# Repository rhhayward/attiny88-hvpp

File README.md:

### Important

The code has been tested on a breadboard, and the original pcb has been
validated to work.  There were two changes made since ordering: 1. The
attiny88 footprint was not wide enough, so it was widened in REV002.
2. The 12v source had left and right reversed - that is fixed in REV003.

Caveat emptor:  If you order PCBs from this, be prepared for them not
to work.  You have been warned.

### ATTINY88 High Voltage Parallel Programmer

This project came from a bricked attiny88. I was changing the fuses, and after
one particular update, none of the methods to program or update fuses worked.
The programmer was unable even to read the signature or fuses. However, the code
was still working, albeit terribly slowly. An LED which previously blinked once
per second was taking minutes to complete a blink cycle. While ATTINY88
microcontrollers are inexpensive and could easily be replaced, I took it as a
challenge to unbrick this one. Reading the datasheet and online, a high voltage
parallel programmer was what was needed, but I couldn't find code or a
schematic, so I worked to get a hvpp programmer working.

This was validated working with a purple pi (off-brand rp2040), a 12v boost
regulator, and the aforementioned bricked ATTINY88. I was then able to use the
`WRITEFUS` command to unbrick the device.  I implemented a few additional
commands as well.  The entire suite of possible commands is not yet available,
but should be doable leveraging the primitives that are already implemented.

### How to

The wiring is laid out in the .ino file. The only additional circuitry is that
the 5v providing the ATTINY88's VCC and the 12v necessary for the RST pin are
switched using a transistor+mosfet. All other wiring is direct from the purple
pi to the ATTINY88.  You can see the full schematic in
`/kicad/attiny88-hvpp.kicad_sch`
(https://kicanvas.org/?github=https%3A%2F%2Fgithub.com%2Frhhayward%2Fattiny88-hvpp%2Ftree%2Fmain%2Fkicad).

Once wired, you canbuild and push the code to the purple pi. I have tested this
using the Arduino IDE 2 with the Raspberry Pi Pico profile which worked for me
with no trouble. With the code running, connect to the purple pi's USB Serial
port.  The code will always prefix its output with a `*`.  It will emit some
help on start.  Once it announces done, you can start issuing commands.

## Commands

* `READSIG` - read and display signature bytes
* `READCAL` - read and display calibration byte
* `READFUS` - read and display fuse and lock bytes
* `READFLA 0x<START> 0x<END>` - read and display flash from start to end
* `WRITEFUS 0x<low> 0x<high> 0x<extended>` - write low high and extended
  fuses, then read and display fuse and lock bytes

## Example execution

```
* starting up
* setting up pin modes and values
* setting up pin modes and values - DONE
* entering programming mode
* entering programming mode - DONE
* Commands:
* READSIG - read signature and write to stdout
* READCAL - read calibration byte and write to stdout
* READFUS - read fuses and lock bytes
* READFLA 0x<START> 0x<END> - read flash from START to END.  Each must be 4 hex digits.
* WRITEFUS 0x<LOW> 0x<HIGH> 0x<EXTENDED> - write LOW HIGH and EXTENDED fuses.  Each must be 2 hex digits.
* * * ready
```
```
READSIG
```
```
* SIGNATURE: 0x1E,0x93,0x11 IDENT: ATTINY88
```
```
READFUS
```
```
* FUSE l=0x37 h=0xDF x=0xFF LOCK 0xFF
```
```
READCAL
```
```
* calibration byte: 0x9D
```
```
READFLA 0x0000 0x0010
```
```
* start=0x0000 end=0x0010
* 0x0000   13c0 22c0 21c0 20c0 1fc0 1ec0 1dc0 1cc0  1bc0 1ac0 19c0 18c0 17c0 16c0 74c0 14c0
```

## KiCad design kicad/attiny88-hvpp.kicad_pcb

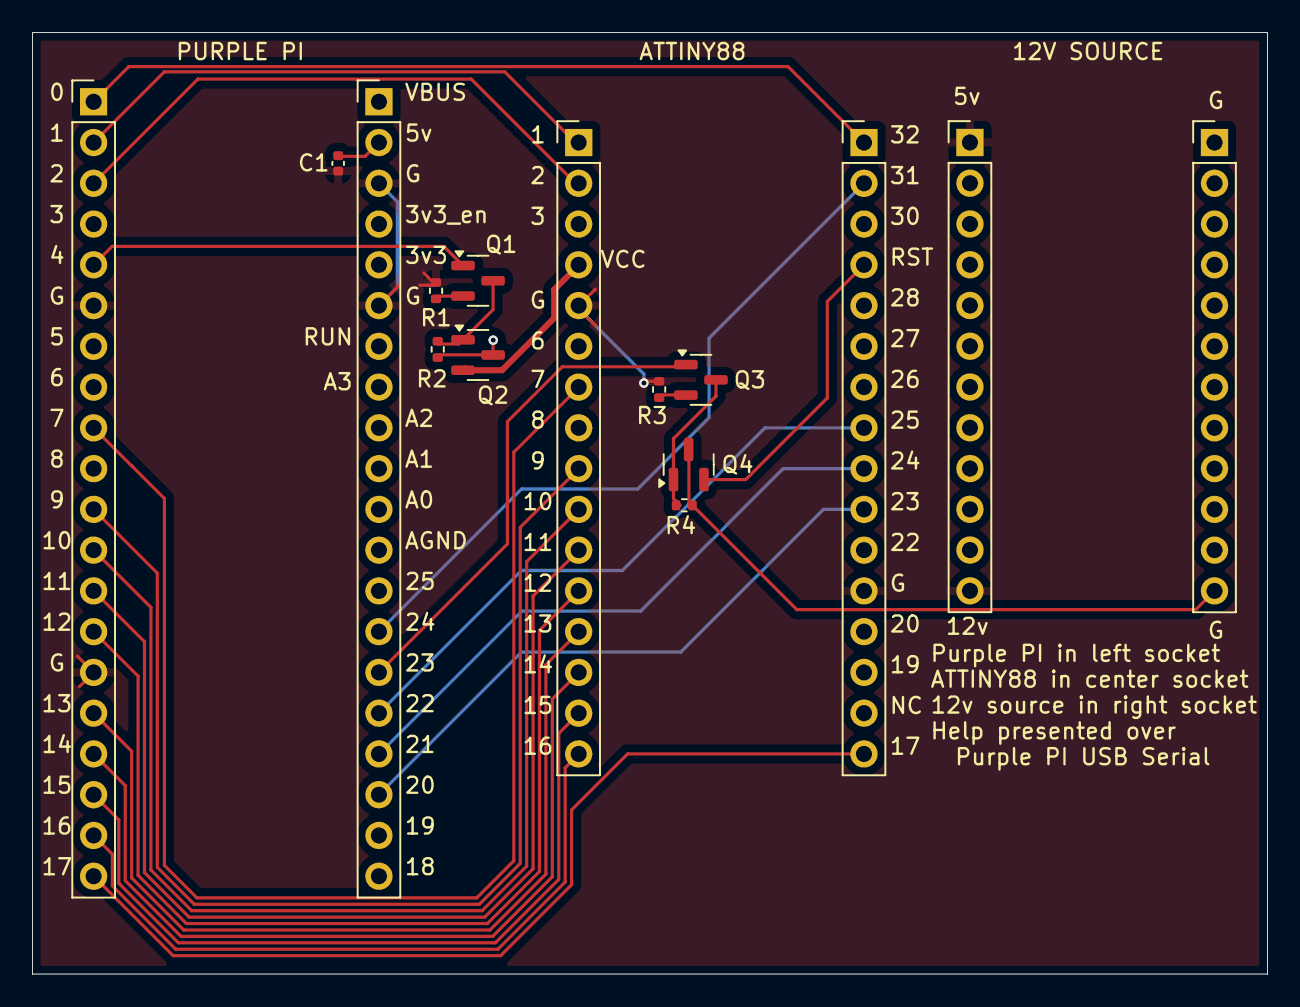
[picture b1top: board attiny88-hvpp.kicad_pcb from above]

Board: 2 copper layers, 77.0 x 58.7 mm, 15 parts (0 on the bottom side), 28 nets.

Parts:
C1: 1u; C_0402_1005Metric
J1: 12v_reg_left_neg; PinHeader_1x12_P2.54mm_Vertical
J2: 12v_reg_right_pos; PinHeader_1x12_P2.54mm_Vertical
J3: purle_pi_left; PinHeader_1x20_P2.54mm_Vertical
J4: purle_pi_right; PinHeader_1x20_P2.54mm_Vertical
J5: ATTINY88_LEFT; PinHeader_1x16_P2.54mm_Vertical
J6: ATTINY88_RIGHT; PinHeader_1x16_P2.54mm_Vertical
Q1, Q3: MMBT3904; SOT-23
Q2, Q4: IRLML6402; SOT-23
R1, R3: 2k2; R_0402_1005Metric
R2, R4: 220k; R_0402_1005Metric

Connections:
/5v: C1.1, J2.1, J4.2, Q2.3 (D), R2.2
/12v: J2.12, Q4.3 (D), R4.2
/ATT5v: J5.4, Q2.2 (S)
/BS1: J3.3, J5.2
/BS2: J4.16, J6.8
/CLKI: J3.9, J5.7
/DATA0: J4.17, J6.9
/DATA1: J4.18, J6.10
/DATA2: J3.20, J6.16
/DATA3: J3.19, J5.16
/DATA4: J3.18, J5.15
/DATA5: J3.17, J5.14
/DATA6: J3.16, J5.13
/DATA7: J3.14, J5.12
/PAGEL: J3.13, J5.11
/RDYBSY: J4.14, J6.2
/XA0: J3.11, J5.9
/XA1: J3.12, J5.10
/pi_pin0: J3.1, J6.1
/pi_pin1: J3.2, J5.1
/pi_pin4: J3.5, Q1.1 (B)
/pi_pin23: J4.15, Q3.1 (B)
/~RST: J6.4, Q4.2 (S)
GND: C1.2, J1.1, J1.12, J3.6, J3.15, J4.3, J4.6, J5.5, J6.12, R1.2, R3.2
unnamed: Q1.3 (C), Q2.1 (G), R2.1
unnamed: Q1.2 (E), R1.1
unnamed: Q3.3 (C), Q4.1 (G), R4.1
unnamed: Q3.2 (E), R3.1

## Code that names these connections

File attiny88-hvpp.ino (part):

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#define WR_PIN 1
#define VCC_PIN 4
#define BS1_PIN 2
#define CLKI_PIN 7
#define XA0_PIN 9
#define XA1_PIN 10
#define PAGEL_PIN 11
#define D0_PIN 12
#define D1_PIN 13
#define D2_PIN 14
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#define D7_PIN 21
#define BS2_PIN 22
#define RST_PIN 23
#define RDYBSY_PIN 24

// mark pin as output, with initial HIGH or LOW
void setOutput(int pin, int initValue) {
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  setOutput(LED_PIN, LOW);
  setOutput(VCC_PIN, LOW);
  setOutput(RST_PIN, LOW);
  setOutput(PAGEL_PIN, LOW);
  setOutput(XA1_PIN, LOW);
  setOutput(XA0_PIN, LOW);
  setOutput(BS1_PIN, LOW);
  setOutput(BS2_PIN, LOW);
  setOutput(CLKI_PIN,LOW);
  setOutput(OE_PIN, LOW);
  setOutput(WR_PIN, LOW);

  // RDYBSY is an input
  pinMode(RDYBSY_PIN, INPUT);
}

// follow procedure to initiate programming mode
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  // setting low is redundant at first, but
  //  still, let's do it for completeness

  // PAGEL=0 ; XA1=0 ; XA0=0 ; BS1=0
  digitalWrite(PAGEL_PIN, LOW);
  digitalWrite(XA1_PIN, LOW);
  digitalWrite(XA0_PIN, LOW);
  digitalWrite(BS1_PIN, LOW);
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
// CLKI low for 1us, high for 1us
void pulseClockPin() {
  digitalWrite(CLKI_PIN, HIGH);
  delayMicroseconds(1);
  digitalWrite(CLKI_PIN, LOW);
  delayMicroseconds(1);
}

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  return value;
}

// read the RDYBSY pin - single value
uint8_t readReadyBusy() {
  uint8_t readyBusy = digitalRead(RDYBSY_PIN);
  return readyBusy;
}

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      // E) Latch Data
      // BS1=1 ; pulse PAGEL high
      digitalWrite(BS1_PIN, HIGH);
      digitalWrite(PAGEL_PIN, HIGH);
      delayMicroseconds(1);
      digitalWrite(PAGEL_PIN, LOW);
      delayMicroseconds(1);
    } // F) Repeat for a page or until done

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
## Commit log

2025-08-07 initial commit - tested and working
2025-08-07 schematic and pcb (untested)
2025-08-07 README.md and some cleanup
2025-08-07 Adding license
2025-08-07 update README.md to show better documentation
2025-08-07 more documentation
2025-08-07 capitalizing calibration byte output to match other output
2025-08-19 had left and right 12v switched
2025-08-19 README cleanup
2025-08-24 added read eeprom, chipErase, consolidated pulseWritePin methodology
2025-08-25 LOADDATA, SHOWDATA, WRITEFLA
